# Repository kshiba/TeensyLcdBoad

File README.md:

# TeensyLcdBoad
2.2 inch and 3.2 inch LCD Connection Board for Teensy

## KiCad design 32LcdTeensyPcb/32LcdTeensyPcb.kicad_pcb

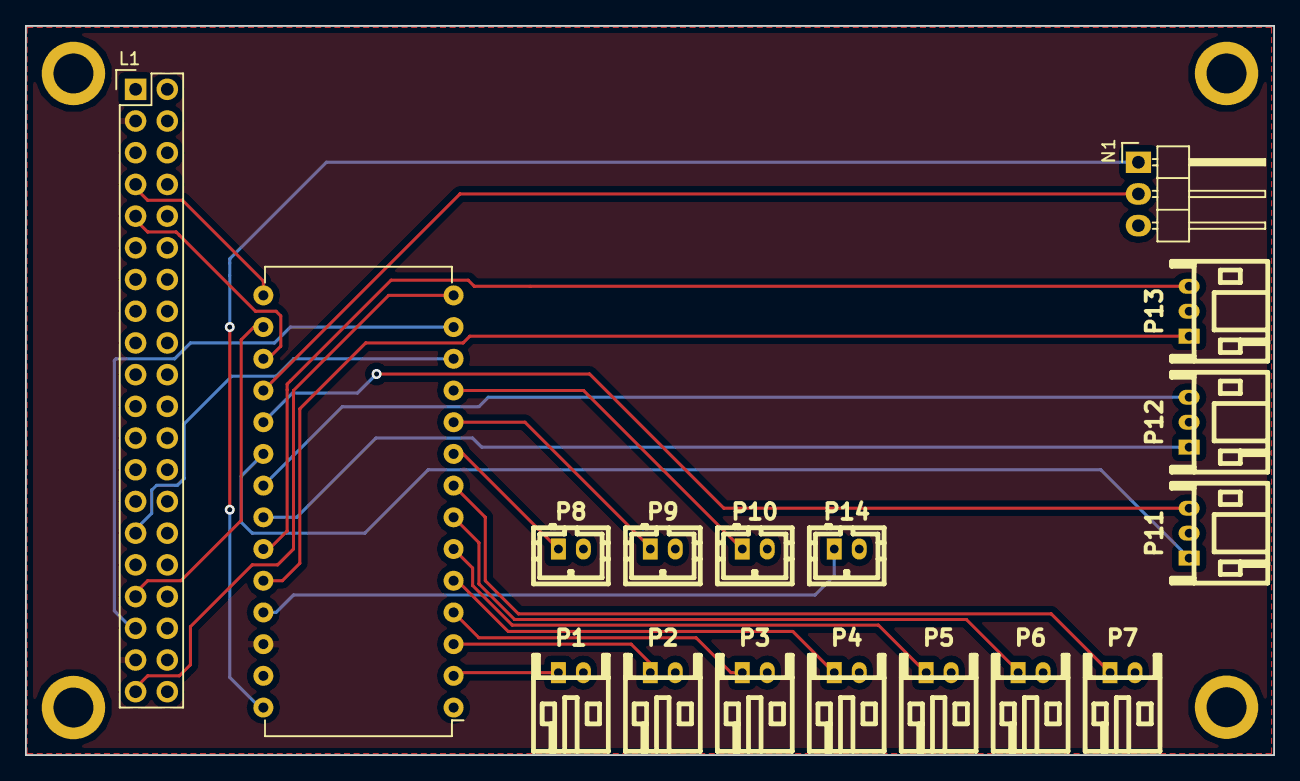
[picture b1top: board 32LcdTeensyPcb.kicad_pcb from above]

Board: 2 copper layers, 100.0 x 58.4 mm, 17 parts (0 on the bottom side), 27 nets.

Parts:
L1: M032C9341B3; M032C9341B3R
N1: CONN_01X03; Pin_Header_Angled_1x03
P1, P2, P3, P4, P5, P6, P7: CONN_01X02; s2b-ph-kl
P8, P9, P10, P14: CONN_01X02; b2b-ph-kl
P11, P12, P13: CONN_01X03; s3b-ph-kl
U1: Teensy3.2/LC; DIP-28_W15.24mm

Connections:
unnamed: L1.1, N1.3, P1.2, P2.2, P3.2, P4.2, P5.2, P6.2, P7.2, P8.2, P9.2, P10.2, P11.2, P12.2, P13.2, P14.2, U1.1
unnamed: L1.4, U1.15
unnamed: L1.5, U1.17
unnamed: L1.15, U1.12
unnamed: L1.17, U1.16
unnamed: L1.18, U1.13
unnamed: L1.2, L1.19, U1.26
unnamed: L1.20, U1.14
unnamed: N1.1, U1.28
unnamed: N1.2, U1.18
unnamed: P1.1, U1.2
unnamed: P2.1, U1.3
unnamed: P3.1, U1.4
unnamed: P4.1, U1.5
unnamed: P5.1, U1.6
unnamed: P6.1, U1.7
unnamed: P7.1, U1.8
unnamed: P8.1, U1.9
unnamed: P9.1, U1.10
unnamed: P10.1, U1.11
unnamed: P11.1, U1.20
unnamed: P11.3, U1.19
unnamed: P12.1, U1.22
unnamed: P12.3, U1.21
unnamed: P13.1, U1.24
unnamed: P13.3, U1.23
unnamed: P14.1, U1.25
